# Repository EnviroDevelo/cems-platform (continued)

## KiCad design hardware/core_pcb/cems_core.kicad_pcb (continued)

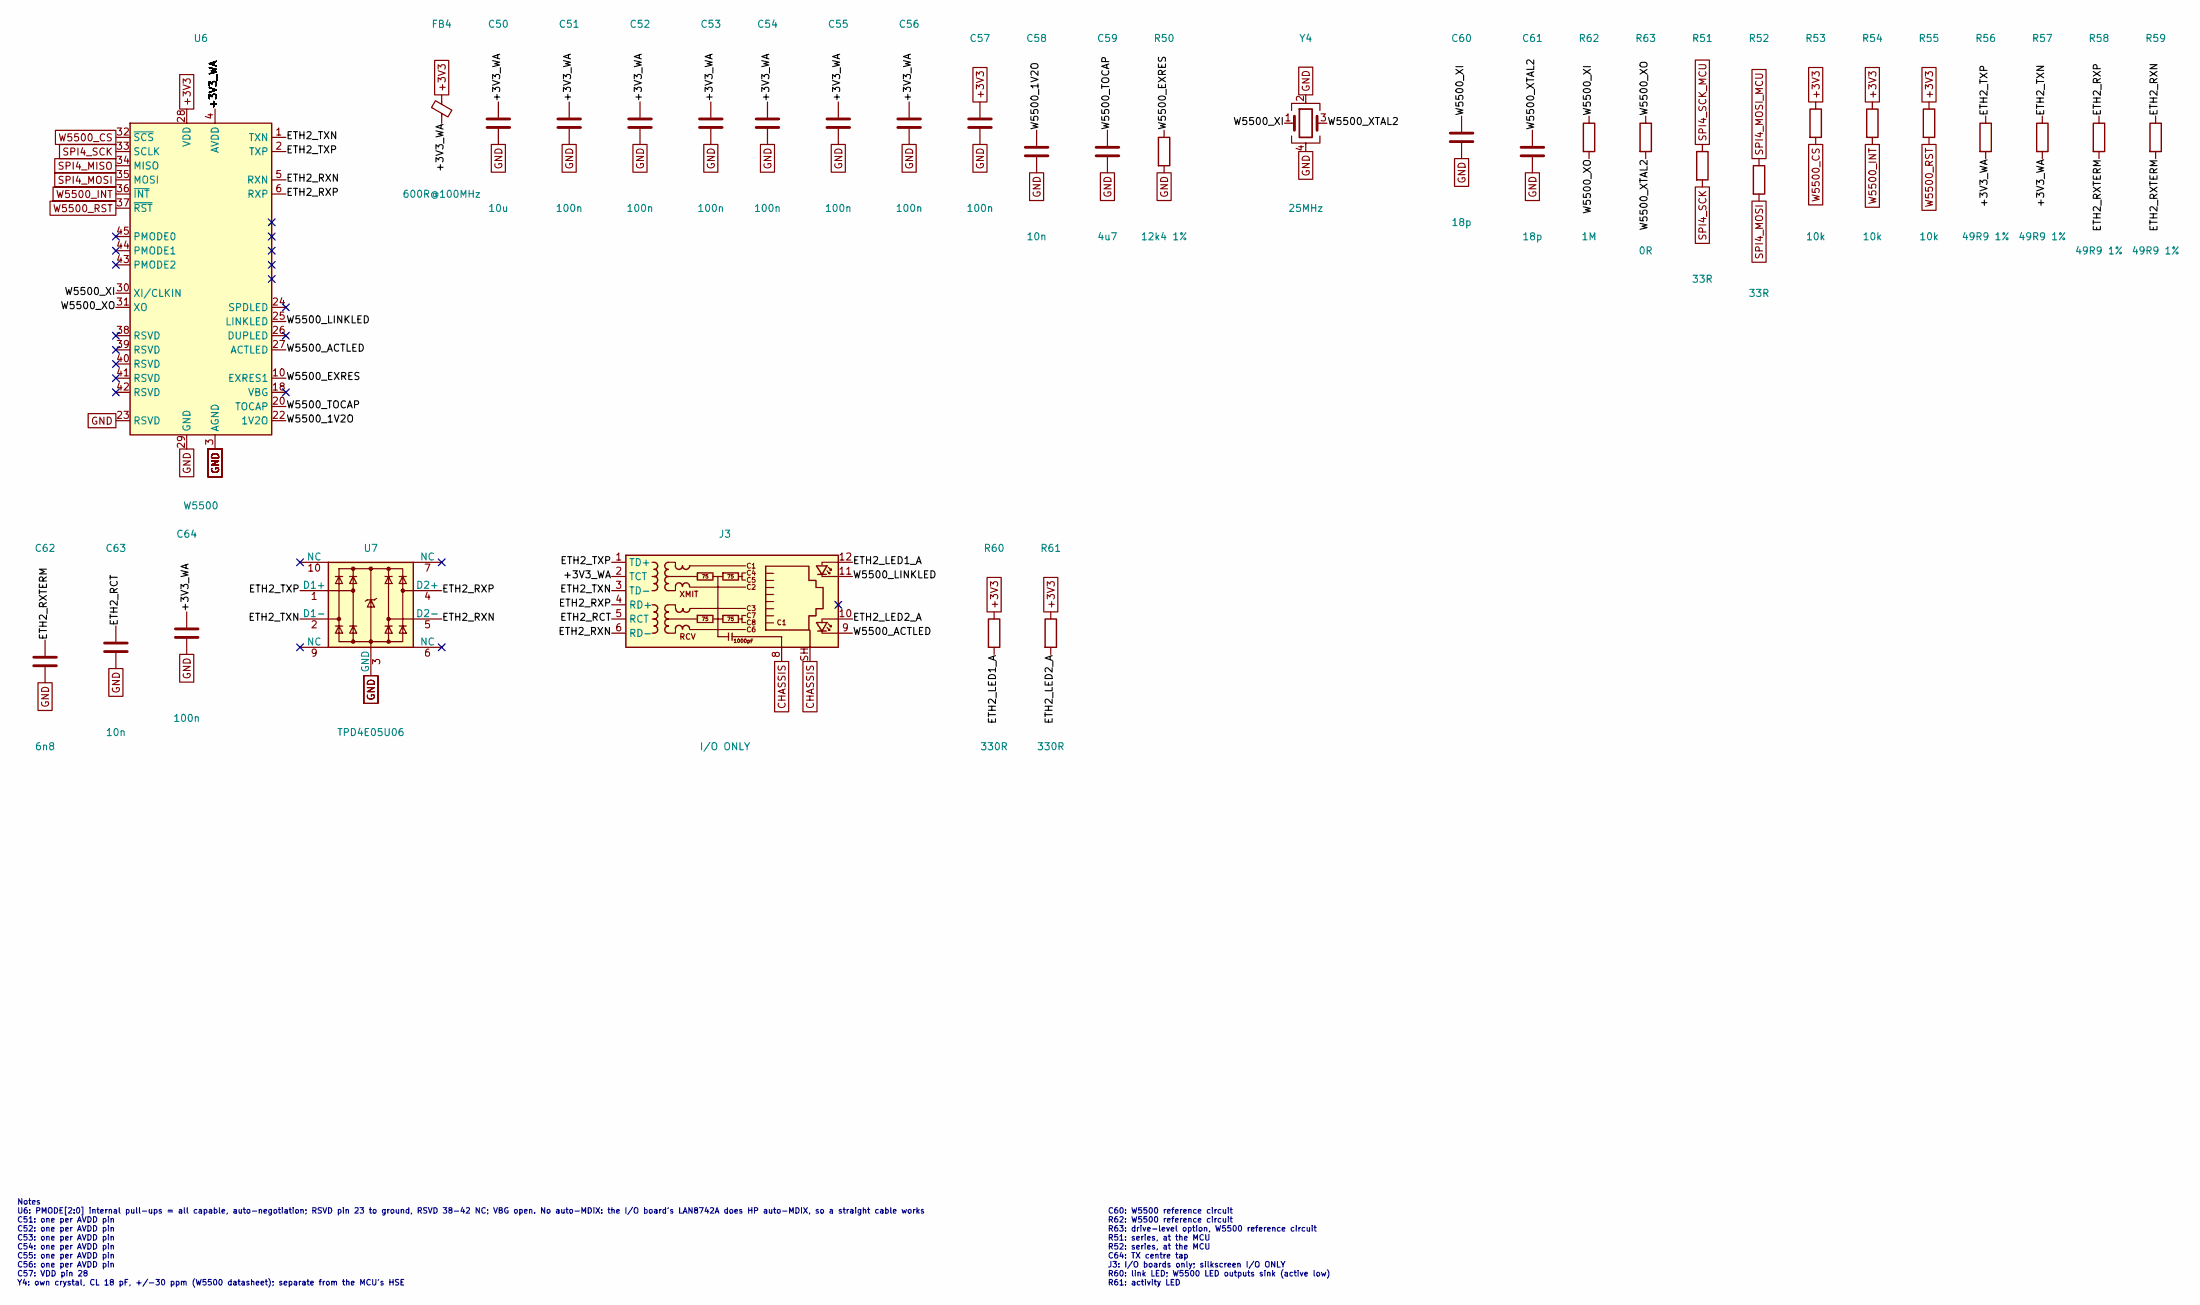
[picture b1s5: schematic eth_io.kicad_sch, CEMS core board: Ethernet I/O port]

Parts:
C50: 10u; C_0805_2012Metric; MPN 10u
C51, C52, C53, C54, C55, C56, C57, C64: 100n; C_0603_1608Metric; MPN 100n
C58, C63: 10n; C_0603_1608Metric; MPN 10n
C59: 4u7; C_0805_2012Metric; MPN 4u7
C60, C61: 18p; C_0603_1608Metric; MPN 18p
C62: 6n8; C_0603_1608Metric; MPN 6n8
FB4: 600R@100MHz; L_0603_1608Metric; MPN 600R@100MHz
J3: I/O ONLY; RJ45_Wuerth_7499010121A_Horizontal; MPN Wurth 7499010121A
R50: 12k4 1%; R_0603_1608Metric; MPN 12k4 1%
R51, R52: 33R; R_0603_1608Metric; MPN 33R
R53, R54, R55: 10k; R_0603_1608Metric; MPN 10k
R56, R57, R58, R59: 49R9 1%; R_0603_1608Metric; MPN 49R9 1%
R60, R61: 330R; R_0603_1608Metric; MPN 330R
R62: 1M; R_0603_1608Metric; MPN 1M
R63: 0R; R_0603_1608Metric; MPN 0R
U6: W5500; LQFP-48_7x7mm_P0.5mm; MPN W5500 (-40 to 85 C)
U7: TPD4E05U06; USON-10_2.5x1.0mm_P0.5mm; MPN TPD4E05U06
Y4: 25MHz; Crystal_SMD_3225-4Pin_3.2x2.5mm; MPN 25MHz

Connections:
+3V3: C57.1, FB4.1, R53.1, R54.1, R55.1, R60.1, R61.1, U6.28 (VDD); also elsewhere on the board
+3V3_WA: C50.1, C51.1, C52.1, C53.1, C54.1, C55.1, C56.1, C64.1, FB4.2, J3.2 (TCT), R56.2, R57.2, U6.4 (AVDD), U6.8 (AVDD), U6.11 (AVDD), U6.15 (AVDD), U6.17 (AVDD), U6.21 (AVDD)
CHASSIS: J3.8, J3.SH; also elsewhere on the board
ETH2_LED1_A: J3.12, R60.2
ETH2_LED2_A: J3.10, R61.2
ETH2_RCT: C63.1, J3.5 (RCT)
ETH2_RXN: J3.6 (RD-), R59.1, U6.5 (RXN), U7.5 (D2-)
ETH2_RXP: J3.4 (RD+), R58.1, U6.6 (RXP), U7.4 (D2+)
ETH2_RXTERM: C62.1, R58.2, R59.2
ETH2_TXN: J3.3 (TD-), R57.1, U6.1 (TXN), U7.2 (D1-)
ETH2_TXP: J3.1 (TD+), R56.1, U6.2 (TXP), U7.1 (D1+)
GND: C50.2, C51.2, C52.2, C53.2, C54.2, C55.2, C56.2, C57.2, C58.2, C59.2, C60.2, C61.2, C62.2, C63.2, C64.2, R50.2, U6.3 (AGND), U6.9 (AGND), U6.14 (AGND), U6.16 (AGND), U6.19 (AGND), U6.23 (RSVD), U6.29 (GND), U6.48 (AGND), U7.3 (GND), U7.8 (GND), Y4.2, Y4.4; also elsewhere on the board
SPI4_MISO: U6.34 (MISO); also elsewhere on the board
SPI4_MOSI: R52.2, U6.35 (MOSI); also elsewhere on the board
SPI4_MOSI_MCU: R52.1; also elsewhere on the board
SPI4_SCK: R51.2, U6.33 (SCLK); also elsewhere on the board
SPI4_SCK_MCU: R51.1; also elsewhere on the board
W5500_1V2O: C58.1, U6.22 (1V2O)
W5500_ACTLED: J3.9, U6.27 (ACTLED)
W5500_CS: R53.2, U6.32 (~SCS); also elsewhere on the board
W5500_EXRES: R50.1, U6.10 (EXRES1)
W5500_INT: R54.2, U6.36 (~INT); also elsewhere on the board
W5500_LINKLED: J3.11, U6.25 (LINKLED)
W5500_RST: R55.2, U6.37 (~RST); also elsewhere on the board
W5500_TOCAP: C59.1, U6.20 (TOCAP)
W5500_XI: C60.1, R62.1, U6.30 (XI/CLKIN), Y4.1
W5500_XO: R62.2, R63.1, U6.31 (XO)
W5500_XTAL2: C61.1, R63.2, Y4.3

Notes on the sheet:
Notes U6: PMODE[2:0] internal pull-ups = all capable, auto-negotiation; RSVD pin 23 to ground, RSVD 38-42 NC; VBG open. No auto-MDIX: the I/O board's LAN8742A does HP auto-MDIX, so a straight cable works C51: one per AVDD pin C52: one per AVDD pin C53: one per AVDD pin C54: one per AVDD pin C55: on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
C60: W5500 reference circuit R62: W5500 reference circuit R63: drive-level option, W5500 reference circuit R51: series, at the MCU R52: series, at the MCU C64: TX centre tap J3: I/O boards only; silkscreen I/O ONLY R60: link LED; W5500 LED outputs sink (active low) R61: activity LED

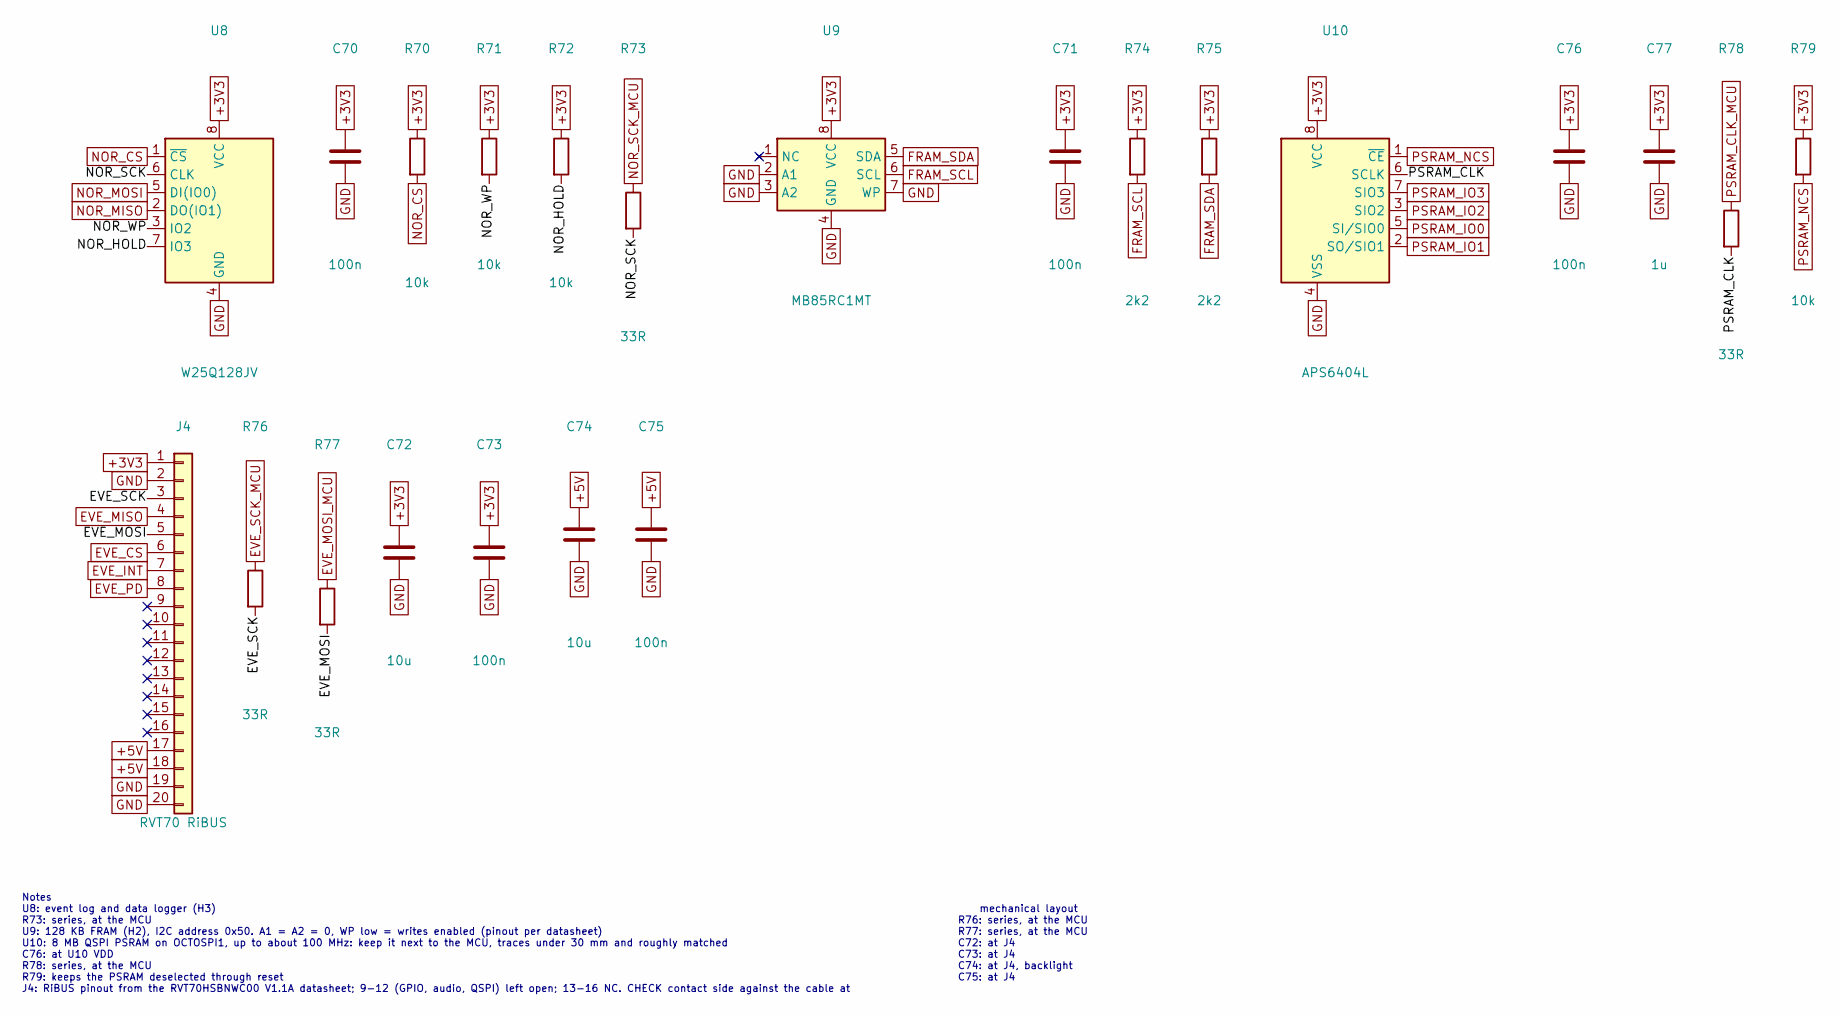
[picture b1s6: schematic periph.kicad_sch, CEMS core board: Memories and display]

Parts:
C70, C71, C73, C75, C76: 100n; C_0603_1608Metric; MPN 100n
C72, C74: 10u; C_0805_2012Metric; MPN 10u
C77: 1u; C_0603_1608Metric; MPN 1u
J4: RVT70 RiBUS; Hirose_FH12-20S-0.5SH_1x20-1MP_P0.50mm_Horizontal; MPN Hirose FH12-20S-0.5SH(55)
R70, R71, R72, R79: 10k; R_0603_1608Metric; MPN 10k
R73, R76, R77, R78: 33R; R_0603_1608Metric; MPN 33R
R74, R75: 2k2; R_0603_1608Metric; MPN 2k2
U8: W25Q128JV; SOIC-8_5.23x5.23mm_P1.27mm; MPN W25Q128JVSIQ
U9: MB85RC1MT; SOIC-8_3.9x4.9mm_P1.27mm; MPN MB85RC1MTPNF
U10: APS6404L; SOIC-8_3.9x4.9mm_P1.27mm; MPN AP Memory APS6404L-3SQR-SN (-ZR for -40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

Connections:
+3V3: C70.1, C71.1, C72.1, C73.1, C76.1, C77.1, J4.1, R70.1, R71.1, R72.1, R74.1, R75.1, R79.1, U8.8 (VCC), U9.8 (VCC), U10.8 (VCC); also elsewhere on the board
+5V: C74.1, C75.1, J4.17, J4.18; also elsewhere on the board
EVE_CS: J4.6; also elsewhere on the board
EVE_INT: J4.7; also elsewhere on the board
EVE_MISO: J4.4; also elsewhere on the board
EVE_MOSI: J4.5, R77.2
EVE_MOSI_MCU: R77.1; also elsewhere on the board
EVE_PD: J4.8; also elsewhere on the board
EVE_SCK: J4.3, R76.2
EVE_SCK_MCU: R76.1; also elsewhere on the board
FRAM_SCL: R74.2, U9.6 (SCL); also elsewhere on the board
FRAM_SDA: R75.2, U9.5 (SDA); also elsewhere on the board
GND: C70.2, C71.2, C72.2, C73.2, C74.2, C75.2, C76.2, C77.2, J4.2, J4.19, J4.20, U8.4 (GND), U9.2 (A1), U9.3 (A2), U9.4 (GND), U9.7 (WP), U10.4 (VSS); also elsewhere on the board
NOR_CS: R70.2, U8.1 (~CS); also elsewhere on the board
NOR_HOLD: R72.2, U8.7 (IO3)
NOR_MISO: U8.2 (DO(IO1)); also elsewhere on the board
NOR_MOSI: U8.5 (DI(IO0)); also elsewhere on the board
NOR_SCK: R73.2, U8.6 (CLK)
NOR_SCK_MCU: R73.1; also elsewhere on the board
NOR_WP: R71.2, U8.3 (IO2)
PSRAM_CLK: R78.2, U10.6 (SCLK)
PSRAM_CLK_MCU: R78.1; also elsewhere on the board
PSRAM_IO0: U10.5 (SI/SIO0); also elsewhere on the board
PSRAM_IO1: U10.2 (SO/SIO1); also elsewhere on the board
PSRAM_IO2: U10.3 (SIO2); also elsewhere on the board
PSRAM_IO3: U10.7 (SIO3); also elsewhere on the board
PSRAM_NCS: R79.2, U10.1 (~CE); also elsewhere on the board

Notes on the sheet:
Notes U8: event log and data logger (H3) R73: series, at the MCU U9: 128 KB FRAM (H2), I2C address 0x50. A1 = A2 = 0, WP low = writes enabled (pinout per datasheet) U10: 8 MB QSPI PSRAM on OCTOSPI1, up to about 100 MHz: keep it next to the MCU, traces under 30 mm and roughly matched C76: at U10 VDD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
mechanical layout R76: series, at the MCU R77: series, at the MCU C72: at J4 C73: at J4 C74: at J4, backlight C75: at J4

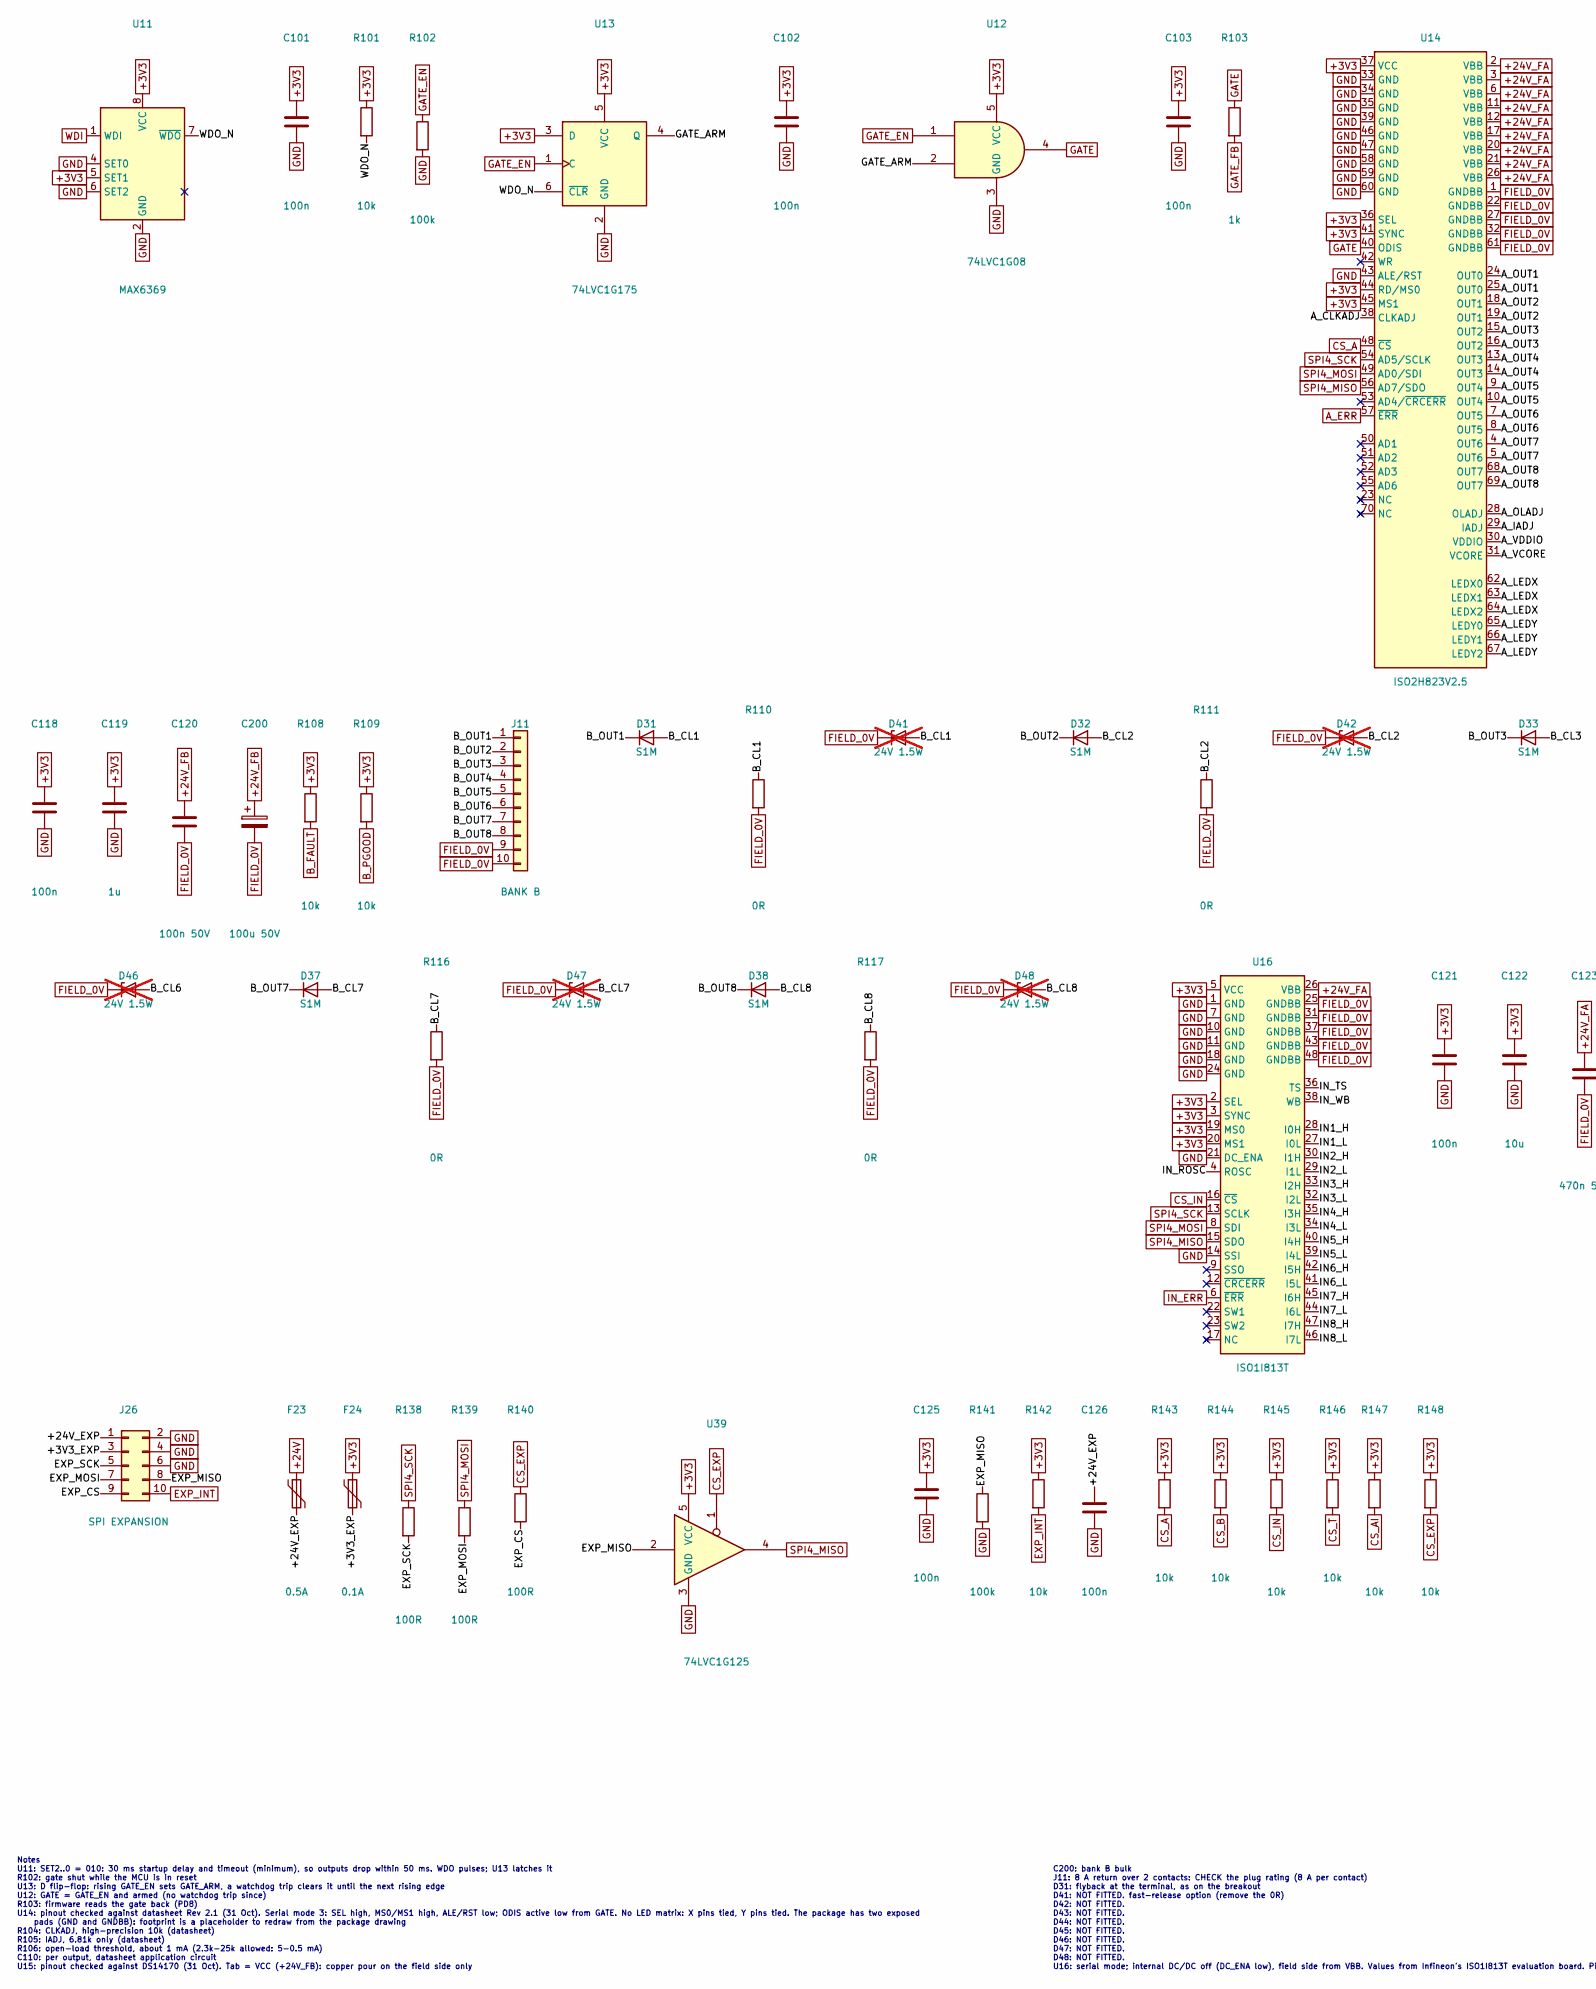
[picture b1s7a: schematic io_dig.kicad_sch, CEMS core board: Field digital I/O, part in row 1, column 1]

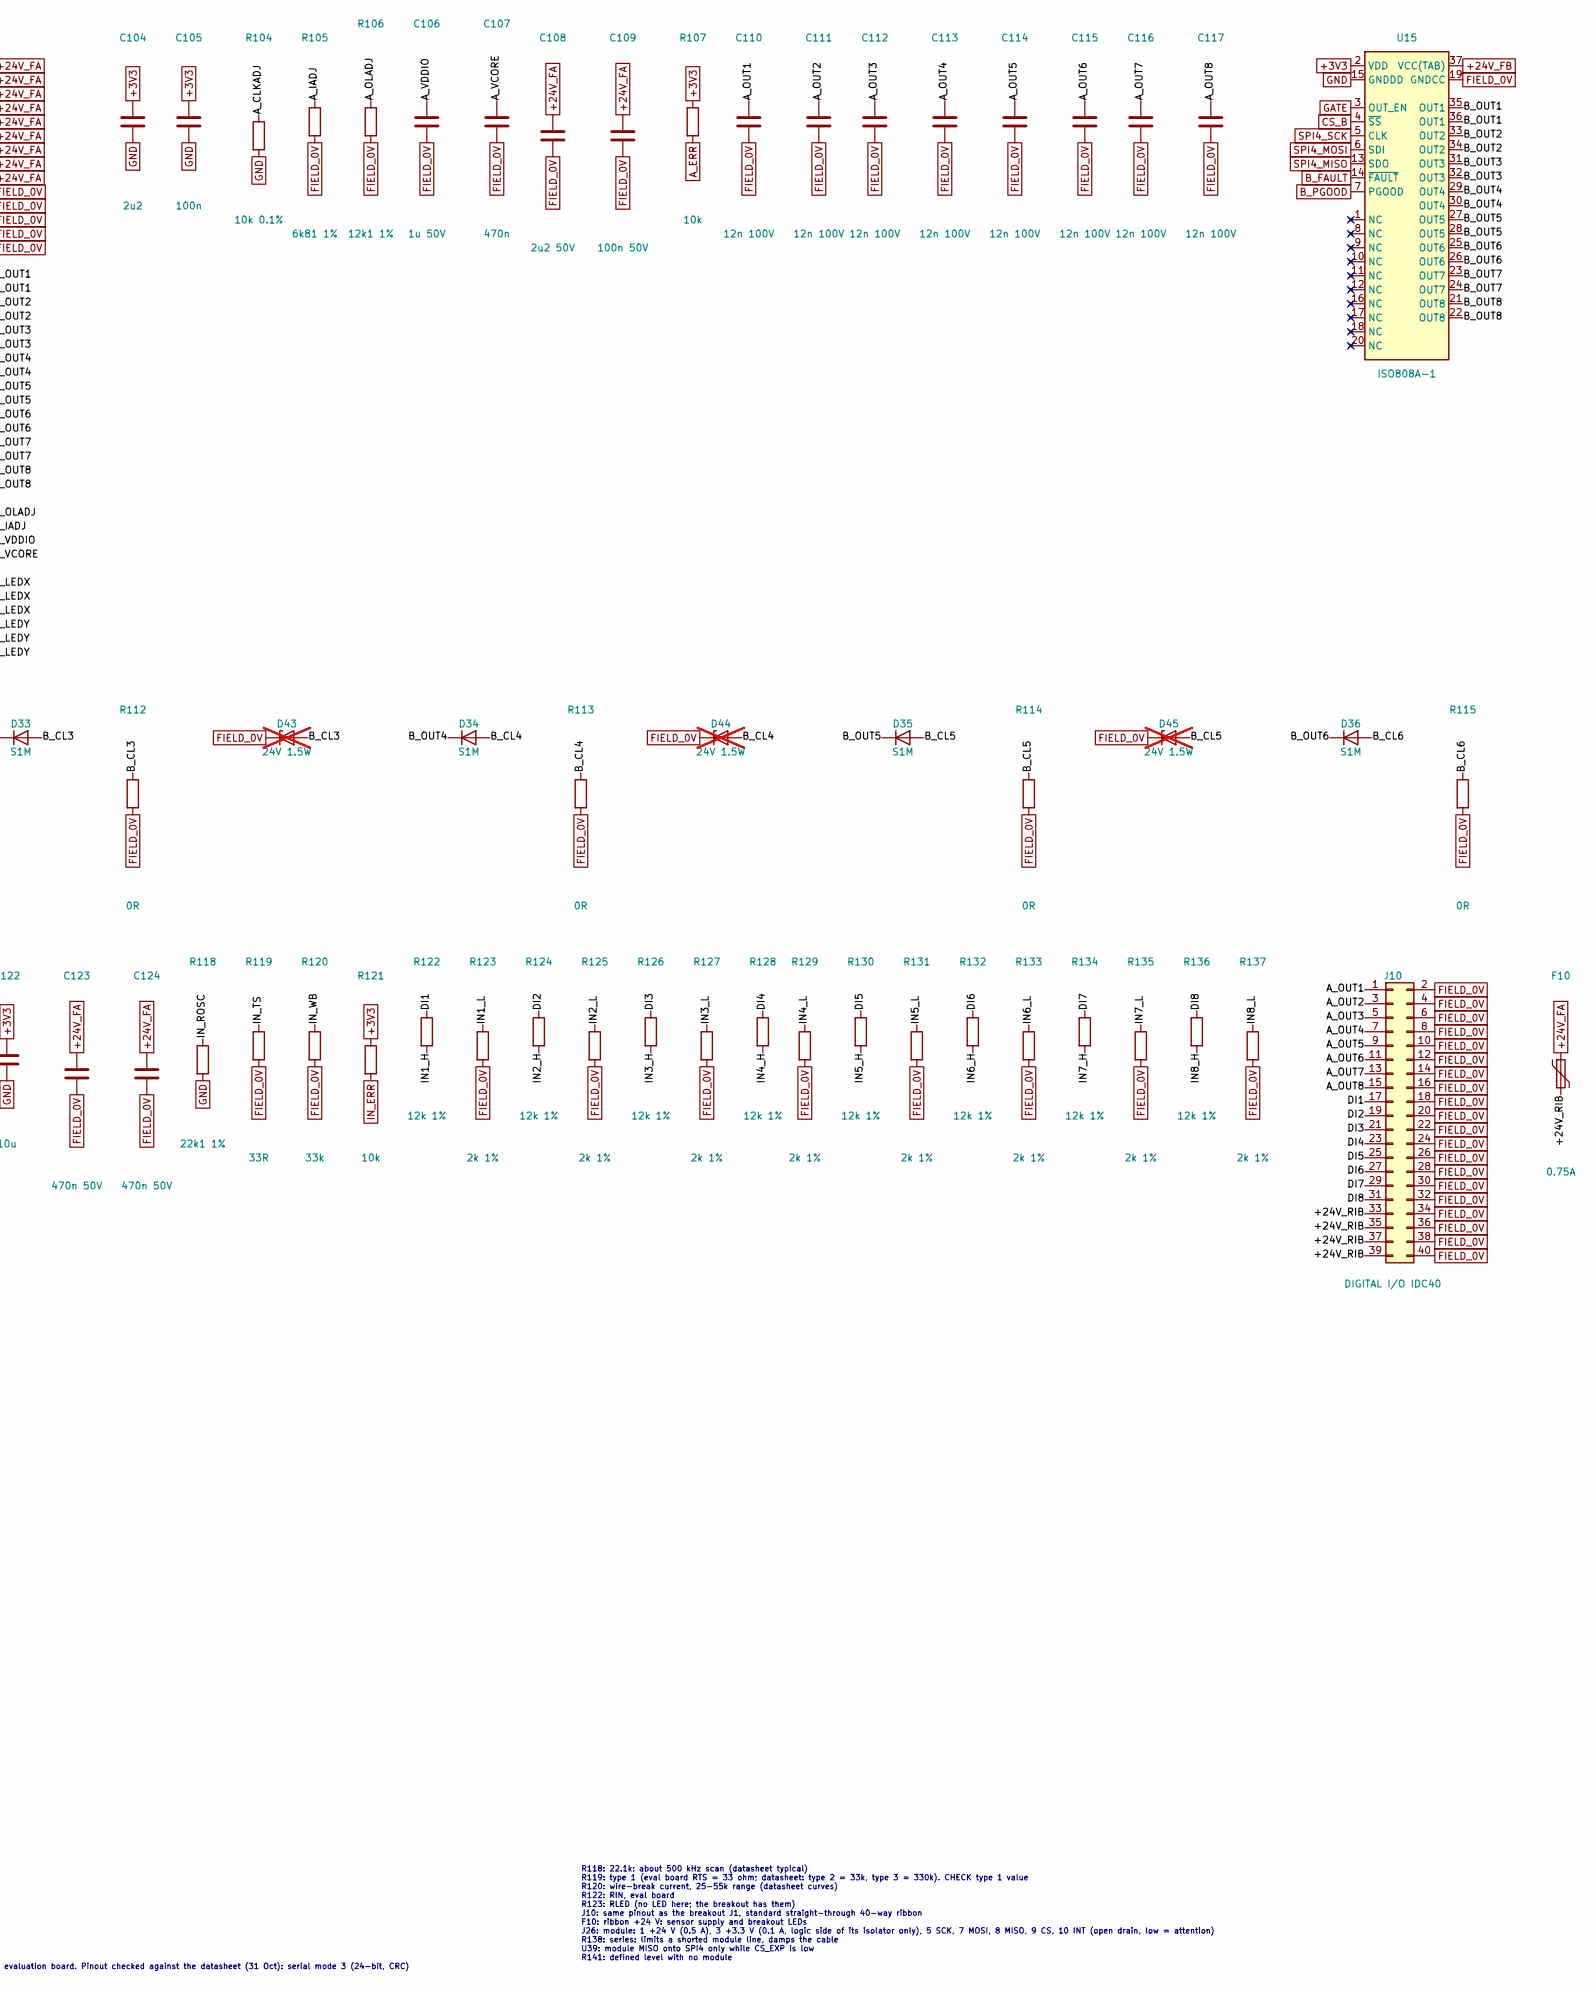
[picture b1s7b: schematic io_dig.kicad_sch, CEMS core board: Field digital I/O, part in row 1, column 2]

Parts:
C101, C102, C103, C105, C118, C121, C125: 100n; C_0603_1608Metric; MPN 100n
C104: 2u2; C_0805_2012Metric; MPN 2u2
C106: 1u 50V; C_0805_2012Metric; MPN 1u 50V
C107: 470n; C_0603_1608Metric; MPN 470n
C108: 2u2 50V; C_1210_3225Metric; MPN 2u2 50V
C109, C120: 100n 50V; C_0603_1608Metric; MPN 100n 50V
C110, C111, C112, C113, C114, C115, C116, C117: 12n 100V; C_0603_1608Metric; MPN 12n 100V
C119: 1u; C_0603_1608Metric; MPN 1u
C122: 10u; C_0805_2012Metric; MPN 10u
C123, C124: 470n 50V; C_0805_2012Metric; MPN 470n 50V
C126: 100n; C_0805_2012Metric; MPN 100n
C200: 100u 50V; CP_Elec_10x10; MPN 100u 50V
D31, D32, D33, D34, D35, D36, D37, D38: S1M; D_SMA; MPN S1M
D41, D42, D43, D44, D45, D46, D47, D48: 24V 1.5W; D_SMB; MPN 1SMB5934BT3; not fitted
F10: 0.75A; Fuse_1812_4532Metric; MPN Bourns MF-MSMF075-2
F23: 0.5A; Fuse_1206_3216Metric; MPN Bourns MF-NSMF050-2
F24: 0.1A; Fuse_1206_3216Metric; MPN Bourns MF-NSMF010-2
J10: DIGITAL I/O IDC40; IDC-Header_2x20_P2.54mm_Latch_Vertical; MPN Wurth 61204022821 (WR-BHD 40-way, long 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
J11: BANK B; PhoenixContact_MCV_1,5_10-G-3.81_1x10_P3.81mm_Vertical; MPN Phoenix MCV 1,5/10-G-3,81 + coded, labe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
J26: SPI EXPANSION; IDC-Header_2x05_P2.54mm_Latch_Vertical; MPN Wurth 61201021621 (WR-BHD 10-way latche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
R101, R107, R108, R109, R121, R142, R143, R144, R145, R146, R147, R148: 10k; R_0603_1608Metric; MPN 10k
R102, R141: 100k; R_0603_1608Metric; MPN 100k
R103: 1k; R_0603_1608Metric; MPN 1k
R104: 10k 0.1%; R_0603_1608Metric; MPN 10k 0.1%
R105: 6k81 1%; R_0603_1608Metric; MPN 6k81 1%
R106: 12k1 1%; R_0603_1608Metric; MPN 12k1 1%
R110, R111, R112, R113, R114, R115, R116, R117: 0R; R_1206_3216Metric; MPN 0R
R118: 22k1 1%; R_0603_1608Metric; MPN 22k1 1%
R119: 33R; R_0603_1608Metric; MPN 33R
R120: 33k; R_0603_1608Metric; MPN 33k
R122, R124, R126, R128, R130, R132, R134, R136: 12k 1%; R_1206_3216Metric; MPN 12k 1%
R123, R125, R127, R129, R131, R133, R135, R137: 2k 1%; R_0603_1608Metric; MPN 2k 1%
R138, R139, R140: 100R; R_0603_1608Metric; MPN 100R
U11: MAX6369; SOT-23-8; MPN MAX6369KA+T
U12: 74LVC1G08; SOT-23-5; MPN SN74LVC1G08DBVR
U13: 74LVC1G175; SOT-23-6; MPN SN74LVC1G175DBVR
U14: ISO2H823V2.5; Infineon_PG-VQFN-70_12x12mm_P0.5mm; MPN Infineon ISO2H823V25XUMA1
U15: ISO808A-1; HSOP-36-1EP_11.0x15.9mm_P0.65mm_SlugDown; MPN ST ISO808A-1TR
U16: ISO1I813T; TSSOP-48_6.1x12.5mm_P0.5mm; MPN Infineon ISO1I813TXUMA1
U39: 74LVC1G125; SOT-23-5; MPN SN74LVC1G125DBVR

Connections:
+3V3: C101.1, C102.1, C103.1, C104.1, C105.1, C118.1, C119.1, C121.1, C122.1, C125.1, F24.1, R101.1, R107.1, R108.1, R109.1, R121.1, R142.1, R143.1, R144.1, R145.1, R146.1, R147.1, R148.1, U11.5 (SET1), U11.8 (VCC), U12.5 (VCC), U13.3 (D), U13.5 (VCC), U14.36 (SEL), U14.37 (VCC), U14.41 (SYNC), U14.44 (RD/MS0), U14.45 (MS1), U15.2 (VDD), U16.2 (SEL), U16.3 (SYNC), U16.5 (VCC), U16.19 (MS0), U16.20 (MS1), U39.5 (VCC); also elsewhere on the board
+3V3_EXP: F24.2, J26.3
+24V: F23.1; also elsewhere on the board
+24V_EXP: C126.1, F23.2, J26.1
+24V_FA: C108.1, C109.1, C123.1, C124.1, F10.1, U14.2 (VBB), U14.3 (VBB), U14.6 (VBB), U14.11 (VBB), U14.12 (VBB), U14.17 (VBB), U14.20 (VBB), U14.21 (VBB), U14.26 (VBB), U16.26 (VBB); also elsewhere on the board
+24V_FB: C120.1, C200.1, U15.37 (VCC(TAB)); also elsewhere on the board
+24V_RIB: F10.2, J10.33, J10.35, J10.37, J10.39
A_CLKADJ: R104.1, U14.38 (CLKADJ)
A_ERR: R107.2, U14.57 (~ERR); also elsewhere on the board
A_IADJ: R105.1, U14.29 (IADJ)
A_LEDX: U14.62 (LEDX0), U14.63 (LEDX1), U14.64 (LEDX2)
A_LEDY: U14.65 (LEDY0), U14.66 (LEDY1), U14.67 (LEDY2)
A_OLADJ: R106.1, U14.28 (OLADJ)
A_OUT1: C110.1, J10.1, U14.24 (OUT0), U14.25 (OUT0)
A_OUT2: C111.1, J10.3, U14.18 (OUT1), U14.19 (OUT1)
A_OUT3: C112.1, J10.5, U14.15 (OUT2), U14.16 (OUT2)
A_OUT4: C113.1, J10.7, U14.13 (OUT3), U14.14 (OUT3)
A_OUT5: C114.1, J10.9, U14.9 (OUT4), U14.10 (OUT4)
A_OUT6: C115.1, J10.11, U14.7 (OUT5), U14.8 (OUT5)
A_OUT7: C116.1, J10.13, U14.4 (OUT6), U14.5 (OUT6)
A_OUT8: C117.1, J10.15, U14.68 (OUT7), U14.69 (OUT7)
A_VCORE: C107.1, U14.31 (VCORE)
A_VDDIO: C106.1, U14.30 (VDDIO)
B_CL1: D31.2 (A), D41.2 (A), R110.1
B_CL2: D32.2 (A), D42.2 (A), R111.1
B_CL3: D33.2 (A), D43.2 (A), R112.1
B_CL4: D34.2 (A), D44.2 (A), R113.1
B_CL5: D35.2 (A), D45.2 (A), R114.1
B_CL6: D36.2 (A), D46.2 (A), R115.1
B_CL7: D37.2 (A), D47.2 (A), R116.1
B_CL8: D38.2 (A), D48.2 (A), R117.1
B_FAULT: R108.2, U15.14 (~FAULT); also elsewhere on the board
B_OUT1: D31.1 (K), J11.1, U15.35 (OUT1), U15.36 (OUT1)
B_OUT2: D32.1 (K), J11.2, U15.33 (OUT2), U15.34 (OUT2)
B_OUT3: D33.1 (K), J11.3, U15.31 (OUT3), U15.32 (OUT3)
B_OUT4: D34.1 (K), J11.4, U15.29 (OUT4), U15.30 (OUT4)
B_OUT5: D35.1 (K), J11.5, U15.27 (OUT5), U15.28 (OUT5)
B_OUT6: D36.1 (K), J11.6, U15.25 (OUT6), U15.26 (OUT6)
B_OUT7: D37.1 (K), J11.7, U15.23 (OUT7), U15.24 (OUT7)
B_OUT8: D38.1 (K), J11.8, U15.21 (OUT8), U15.22 (OUT8)
B_PGOOD: R109.2, U15.7 (PGOOD); also elsewhere on the board
CS_A: R143.2, U14.48 (~CS); also elsewhere on the board
CS_AI: R147.2; also elsewhere on the board
CS_B: R144.2, U15.4 (~SS); also elsewhere on the board
CS_EXP: R140.1, R148.2, U39.1; also elsewhere on the board
CS_IN: R145.2, U16.16 (~CS); also elsewhere on the board
CS_T: R146.2; also elsewhere on the board
DI1: J10.17, R122.1
DI2: J10.19, R124.1
DI3: J10.21, R126.1
DI4: J10.23, R128.1
DI5: J10.25, R130.1
DI6: J10.27, R132.1
DI7: J10.29, R134.1
DI8: J10.31, R136.1
EXP_CS: J26.9, R140.2
EXP_INT: J26.10, R142.2; also elsewhere on the board
EXP_MISO: J26.8, R141.1, U39.2
EXP_MOSI: J26.7, R139.2
EXP_SCK: J26.5, R138.2
FIELD_0V: C106.2, C107.2, C108.2, C109.2, C110.2, C111.2, C112.2, C113.2, C114.2, C115.2, C116.2, C117.2, C120.2, C123.2, C124.2, C200.2, D41.1 (K), D42.1 (K), D43.1 (K), D44.1 (K), D45.1 (K), D46.1 (K), D47.1 (K), D48.1 (K), J10.2, J10.4, J10.6, J10.8, J10.10, J10.12, J10.14, J10.16, J10.18, J10.20, J10.22, J10.24, J10.26, J10.28, J10.30, J10.32, J10.34, J10.36, J10.38, J10.40, J11.9, J11.10, R105.2, R106.2, R110.2, R111.2, R112.2, R113.2, R114.2, R115.2, R116.2, R117.2, R119.2, R120.2, R123.2, R125.2, R127.2, R129.2, R131.2, R133.2, R135.2, R137.2, U14.1 (GNDBB), U14.22 (GNDBB), U14.27 (GNDBB), U14.32 (GNDBB), U14.61 (GNDBB), U15.19 (GNDCC), U16.25 (GNDBB), U16.31 (GNDBB), U16.37 (GNDBB), U16.43 (GNDBB), U16.48 (GNDBB); also elsewhere on the board
GATE: R103.1, U12.4, U14.40 (ODIS), U15.3 (OUT_EN); also elsewhere on the board
GATE_ARM: U12.2, U13.4 (Q)
GATE_EN: R102.1, U12.1, U13.1 (C); also elsewhere on the board
GATE_FB: R103.2; also elsewhere on the board
GND: C101.2, C102.2, C103.2, C104.2, C105.2, C118.2, C119.2, C121.2, C122.2, C125.2, C126.2, J26.2, J26.4, J26.6, R102.2, R104.2, R118.2, R141.2, U11.2 (GND), U11.4 (SET0), U11.6 (SET2), U12.3 (GND), U13.2 (GND), U14.33 (GND), U14.34 (GND), U14.35 (GND), U14.39 (GND), U14.43 (ALE/RST), U14.46 (GND), U14.47 (GND), U14.58 (GND), U14.59 (GND), U14.60 (GND), U15.15 (GNDDD), U16.1 (GND), U16.7 (GND), U16.10 (GND), U16.11 (GND), U16.14 (SSI), U16.18 (GND), U16.21 (DC_ENA), U16.24 (GND), U39.3 (GND); also elsewhere on the board
IN1_H: R122.2, U16.28 (I0H)
IN1_L: R123.1, U16.27 (I0L)
IN2_H: R124.2, U16.30 (I1H)
IN2_L: R125.1, U16.29 (I1L)
IN3_H: R126.2, U16.33 (I2H)
IN3_L: R127.1, U16.32 (I2L)
IN4_H: R128.2, U16.35 (I3H)
IN4_L: R129.1, U16.34 (I3L)
IN5_H: R130.2, U16.40 (I4H)
IN5_L: R131.1, U16.39 (I4L)
IN6_H: R132.2, U16.42 (I5H)
IN6_L: R133.1, U16.41 (I5L)
IN7_H: R134.2, U16.45 (I6H)
IN7_L: R135.1, U16.44 (I6L)
IN8_H: R136.2, U16.47 (I7H)
IN8_L: R137.1, U16.46 (I7L)
IN_ERR: R121.2, U16.6 (~ERR); also elsewhere on the board
IN_ROSC: R118.1, U16.4 (ROSC)
IN_TS: R119.1, U16.36 (TS)
IN_WB: R120.1, U16.38 (WB)
SPI4_MISO: U14.56 (AD7/SDO), U15.13 (SDO), U16.15 (SDO), U39.4; also elsewhere on the board
SPI4_MOSI: R139.1, U14.49 (AD0/SDI), U15.6 (SDI), U16.8 (SDI); also elsewhere on the board
SPI4_SCK: R138.1, U14.54 (AD5/SCLK), U15.5 (CLK), U16.13 (SCLK); also elsewhere on the board
WDI: U11.1 (WDI); also elsewhere on the board
WDO_N: R101.2, U11.7 (~WDO), U13.6 (~CLR)

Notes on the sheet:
Notes U11: SET2..0 = 010: 30 ms startup delay and timeout (minimum), so outputs drop within 50 ms. WDO pulses; U13 latches it R102: gate shut while the MCU is in reset U13: D flip-flop: rising GATE_EN sets GATE_ARM, a watchdog trip clears it until the next rising edge U12: GATE = GATE_EN and armed 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
C200: bank B bulk J11: 8 A return over 2 contacts: CHECK the plug rating (8 A per contact) D31: flyback at the terminal, as on the breakout D41: NOT FITTED. fast-release option (remove the 0R) D42: NOT FITTED. D43: NOT FITTED. D44: NOT FITTED. D45: NOT FITTED. D46: NOT FITTED. D47: NOT FITTED. D48: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
R118: 22.1k: about 500 kHz scan (datasheet typical) R119: type 1 (eval board RTS = 33 ohm; datasheet: type 2 = 33k, type 3 = 330k). CHECK type 1 value R120: wire-break current, 25-55k range (datasheet curves) R122: RIN, eval board R123: RLED (no LED here; the breakout has them) J10: same pinout as 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
